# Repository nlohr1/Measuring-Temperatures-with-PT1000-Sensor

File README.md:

# Measuring Temperatures with PT1000-Sensor v1.1
High accurate Temperature-measures (down to ±0.1°C) with Adafruits MAX31865 Module and a *small* PT1000-Sensor,
using an ATMega328(Arduino) and an OLED-Module (connected via I2C) to view Reults in °C.

A description + instructions of the MAX31865 Module from Adafruit can be read on their site:
https://learn.adafruit.com/adafruit-max31865-rtd-pt100-amplifier/

I used a *small* PT1000-Sensor from Delta-R (=> https://delta-r.de/de/elemente/pt/pt-1.000/pt-1000-2b/38/2x2-pt1000-2b-7500c),
due to the fact that a PT1000 has more voltage amplitude (to measure) as a PT100, so precision of reading per default is more precise
and has fewer noise and resistances (on cables). A small Sensor like this also is much faster reaching the objects temperature
to measure (fewer time-loss waiting for "ready").
But preciseness of reading the real temp. also depends on how we connect the Sensor physically to the measured Object.
I use a small bit of Thermal Paste between the PT1000-Sensor and the measuring-object (Att.: Sensor connected before heating the object ;-).

The translation of the small read voltage isn't analogue as used often in old boards with PTCs (PositiveTemperatureCoefficient Sensor)
obtaining bad results because of "noise", added resistances and offset-voltages from cables, etc. as described above.
So through SPI-Connection (4 cables + GND/V+) and short connections there are not so many possible measuring faults.
The Arduino-Code from Adafruit is really simple, (see file "Adafruit_MAX31865_PT100-P1000-RTD-Sensor.ino"), using the Adafruit-Library:
https://github.com/adafruit/Adafruit_MAX31865 (download).

Converting the Readings (measured values) for the small I2C-OLED-Output (128x64px):
I choosed Temperature in °C to be the value from interest. For good readability I used a bigger and (IMHO) nicer font as the
default fonts provided from Adafruit-GFX-library.
Downloaded "FreeSansBold.ttf", modified with the (free) App "FontForge" using therein only the essential necessary letters: number
44 to 67 from ASCII-Table) to minify RAM-consumption in the ATMega328.
I compiled this resulted .ttf-font with "fontconvert.exe" to a usable Bitmap-font, named "FreeSnBld12pt7b.h" to use for the OLED.
If you like it, feel free to use it without restrictions besides the licensing of the original font ("FreeSansBold.ttf"), which is
(IMHO) a nicer Sans-Serif font on a small OLED as used.

## Measuring alternative with analog Amplifier
For anyone who prefers a more traditional method, amplifying measured voltages with an Analog-Amplifier in combination with (my) preferred
PT1000-Sensor-Type, the alternative (for shorter wires) is to use a Differentiation Amplifier, so also this method may cancel Offset-Voltages
and Noises. I used an ADS1115 SMD-IC as amplifier in combination with a TL431-LDO (SMD-IC), which provides the stabilized 1,000V reference-voltage
through a following Current/Voltage OpAmp (LMV321) network to one of the two Input-Pins of the ADS1115-Amplifier, therefore providing this
high-stablizized voltage as 1,000 milliAmpere to the PT-1000 Sensor, beeing capable to output highly reliable (reference-)values - with the
same principle as above through I²C-wires to the Arduino.

With two identical PT1000-Sensors (and translating-methods as described), both attached together it is relatively clear that errors are minimized reliably - *if* both
Sensors also are coupled together with Thermal paste inside a heated-pipe (⇒ as "thermocouple"-pipe, turned with the lathe from a 1/4"-Cu-Pipe
as soldering-tip-attachment "micro-oven") – and if both values finally are displaying nearly the same or similar values on the temperature-coordinate.
Attached a schematic to turn on the lathe with a 1/4"-Cu-pipe (min. 50mm length, to obtain a 35mm-pipe).

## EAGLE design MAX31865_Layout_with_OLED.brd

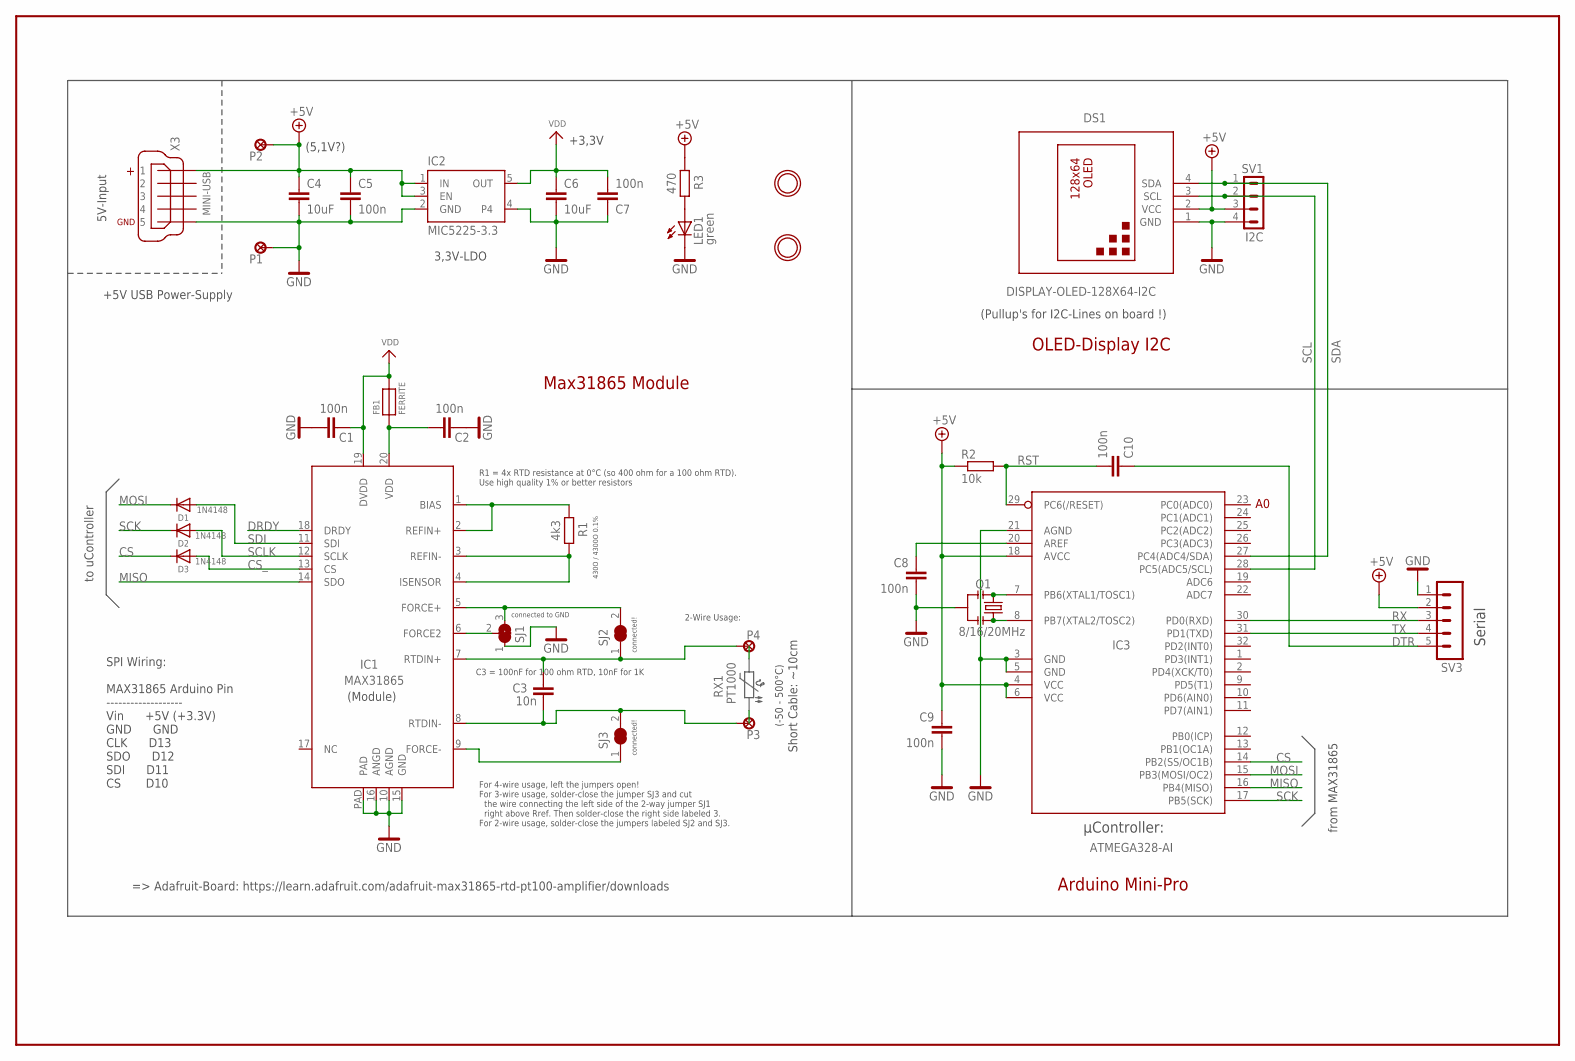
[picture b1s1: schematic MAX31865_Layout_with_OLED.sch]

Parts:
C1, C2, C5, C7, C8, C9, C10: 100n; C0603
C3: 10n; C0603
C4: 10uF; C0805
C6: 10uF; C0603
D1, D2, D3: 1N4148; SOD-323
DS1: DISPLAY-OLED-128X64-I2C
FB1: FERRITE; 0603
IC1: MAX31865; QFN20_4MM_0.65MM
IC2: MIC5225-3.3; SOT23-5
IC3: ATMEGA328-AI; TQFP32-08
LED1: green; CHIPLED_0805
P1, P2, P3, P4: LSP15
Q1: 8/16/20MHz; RESONATOR-SMD-1:1
R1: 4k3; R0603
R2: 10k; R0603
R3: 470; R0603
SJ1: SOLDERJUMPER_2WAY; SOLDERJUMPER_2WAY_OPEN_NOPASTE
SJ2, SJ3: SOLDERJUMPER; SOLDERJUMPER_ARROW_NOPASTE
SV1: I2C; MA04-1
SV3: MA05-1
U$2, U$19: MOUNTINGHOLE2.5; MOUNTINGHOLE_2.5_PLATED
X3: MINI-USB; 32005-201

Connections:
+5V: C4.1, C5.1, C9.1, DS1.2 (VCC), IC2.1 (IN), IC2.3 (EN), IC3.4 (VCC), IC3.6 (VCC), IC3.18 (AVCC), P2.P$1, R2.1, R3.1, SV1.3, SV3.2, X3.1
AREF: C8.1, IC3.20 (AREF)
CS: D3.C, IC3.14 (PB2(SS/OC1B))
CS_: D3.A, IC1.13 (CS)
DRDY: IC1.18 (DRDY)
DTR: C10.1, SV3.5
FORCE2: IC1.6 (FORCE2), SJ1.2
FORCE+: IC1.5 (FORCE+), SJ1.3, SJ2.2
FORCE-: IC1.9 (FORCE-), SJ3.1
GND: C1.2, C2.1, C4.2, C5.2, C6.2, C7.1, C8.2, C9.2, DS1.1 (GND), IC1.10 (AGND), IC1.15 (GND), IC1.16 (ANGD), IC1.PAD, IC2.2 (GND), IC2.4, IC3.3 (GND), IC3.5 (GND), IC3.21 (AGND), LED1.C, P1.P$1, Q1.2, SJ1.1, SV1.4, SV3.1, X3.5
MISO: IC1.14 (SDO), IC3.16 (PB4(MISO))
MOSI: D1.C, IC3.15 (PB3(MOSI/OC2))
unnamed: C2.2, FB1.1, IC1.20 (VDD)
unnamed: IC1.1 (BIAS), IC1.2 (REFIN+), R1.1
unnamed: IC1.3 (REFIN-), IC1.4 (ISENSOR), R1.2
unnamed: IC3.7 (PB6(XTAL1/TOSC1)), Q1.1
unnamed: IC3.8 (PB7(XTAL2/TOSC2)), Q1.3
unnamed: LED1.A, R3.2
RST: C10.2, IC3.29 (PC6(/RESET)), R2.2
RTDIN+: C3.1, IC1.7 (RTDIN+), P4.P$1, SJ2.1
RTDIN-: C3.2, IC1.8 (RTDIN-), P3.P$1, SJ3.2
RX: IC3.30 (PD0(RXD)), SV3.3
SCK: D2.C, IC3.17 (PB5(SCK))
SCL: DS1.3 (SCL), IC3.28 (PC5(ADC5/SCL)), SV1.2
SCLK: D2.A, IC1.12 (SCLK)
SDA: DS1.4 (SDA), IC3.27 (PC4(ADC4/SDA)), SV1.1
SDI: D1.A, IC1.11 (SDI)
TX: IC3.31 (PD1(TXD)), SV3.4
VDD: C1.1, C6.1, C7.2, FB1.2, IC1.19 (DVDD), IC2.5 (OUT)

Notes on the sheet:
µController:
(-50 - 500°C)
Short Cable: ~10cm
C3 = 100nF for 100 ohm RTD, 10nF for 1K
R1 = 4x RTD resistance at 0°C (so 400 ohm for a 100 ohm RTD). Use high quality 1% or better resistors
(5,1V?)
5V-Input
Serial
(Module)
connected!
to uController
=> Adafruit-Board: https://learn.adafruit.com/adafruit-max31865-rtd-pt100-amplifier/downloads
+5V USB Power-Supply
3,3V-LDO
+3,3V
connected to GND
For 4-wire usage, left the jumpers open! For 3-wire usage, solder-close the jumper SJ3 and cut the wire connecting the left side of the 2-way jumper SJ1 right above Rref. Then solder-close the right side labeled 3. For 2-wire usage, solder-close the jumpers labeled SJ2 and SJ3.
2-Wire Usage:
(Pullup's for I2C-Lines on board !)
430O / 4300O 0.1%
SPI Wiring: MAX31865 Arduino Pin ------------------- Vin +5V (+3.3V) GND GND CLK D13 SDO D12 SDI D11 CS D10
Max31865 Module
Arduino Mini-Pro
OLED-Display I2C
from MAX31865

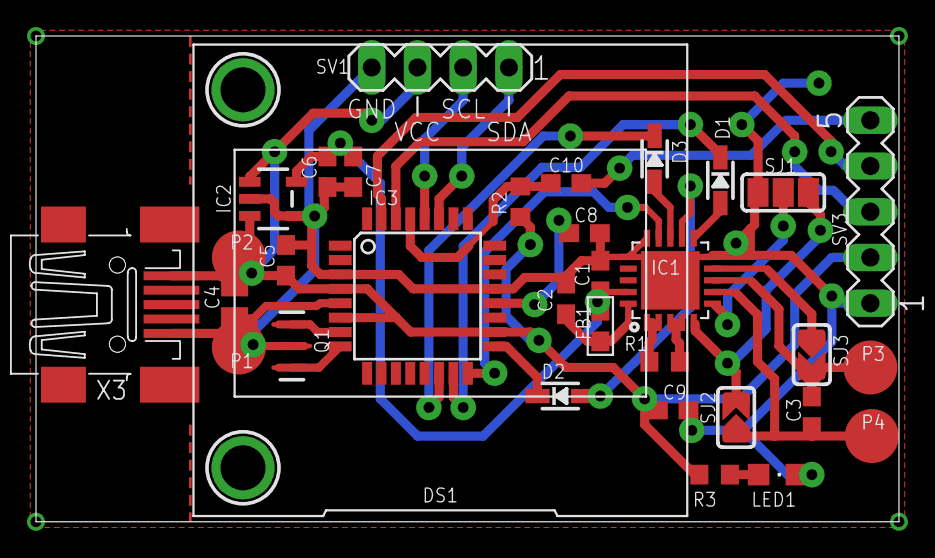
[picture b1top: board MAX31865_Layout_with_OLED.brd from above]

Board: 2 copper layers, 47.9 x 27.0 mm, 35 parts (0 on the bottom side), 28 nets.

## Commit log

2021-01-25 Add files via upload
    With the Adafruits "MAX31865" Module it is possible to measure temperatures with high accuracy (within ±0.1°C), from -40°C up to 750°C, here converted to a readable format with a DIY-Arduino-Board an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
    I use it to control the measures from NTC3950 measured f.ex. on 3D-Printers extruders, heaters (oven), etc.
2021-01-26 Add files via upload
    Now apart of Serial-Monitor added the OLED-Display, showing additional Wiring (Foto) and adding code to the (original Adafruit) Program-Sketch.

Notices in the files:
parts and their libraries:
microbuilder: This work is placed in the public domain, and may be freely used for commercial and non-commercial work with the following conditions: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
diy-modules: Released under the Creative Commons Attribution 4.0 International License: http://creativecommons.org/licenses/by/4.0
